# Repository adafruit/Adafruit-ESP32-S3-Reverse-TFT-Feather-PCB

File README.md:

## Adafruit ESP32-S3 Reverse TFT Feather - 4MB Flash, 2MB PSRAM, STEMMA QT PCB

<a href="http://www.adafruit.com/products/5691"><br/>
Click here to purchase one from the Adafruit shop</a>

PCB files for the Adafruit ESP32-S3 Reverse TFT Feather - 4MB Flash, 2MB PSRAM, STEMMA QT. 

Format is EagleCAD schematic and board layout
* https://www.adafruit.com/product/5691

### Description

Like Missy Elliot, we like to "put our [Feather] down, flip it and reverse it" and that's exactly what we've done with this new development board. It's basically our ESP32-S3 TFT Feather but with the 240x135 color TFT display on the back-side not the front-side. That makes it great for panel-mounted projects, particularly since we've also got some space for 3 buttons to go along. It's like an all-in-one display interface dev board, powered by the fantastic ESP32-S3 WIFI module.

This Feather comes with native USB and 4 MB Flash + 2 MB of PSRAM, so it is perfect for use with CircuitPython or Arduino with low-cost WiFi. Native USB means it can act like a keyboard or a disk drive. WiFi means it's awesome for IoT projects. And Feather means it works with the large community of Feather Wings for expandability.

The ESP32-S3 is a highly-integrated, low-power, 2.4 GHz Wi-Fi/BLE System-on-Chip (SoC) solution that has built-in native USB as well as some other interesting new technologies like Time of Flight distance measurements and AI acceleration. With its state-of-the-art power and RF performance, this SoC is an ideal choice for a wide variety of application scenarios relating to the Internet of Things (IoT), wearable electronics, and smart homes.

The Feather ESP32-S3 has a dual-core 240 MHz chip, so it is comparable to ESP32's dual-core. However, there is no Bluetooth Classic support, only Bluetooth LE. This chip is a great step up from the earlier ESP32-S2! This ESP32-S3 mini-module we are using on the Feather comes with 4 MB flash and 2 MB PSRAM, as well as lots of 512KB of SRAM so it's perfect for use with CircuitPython support or any time massive buffers are needed: for fast memory access use SRAM, for slower-but-roomier access use PSRAM. It's also great for use in ESP-IDF or with Arduino support.

The color TFT is connected to the SPI pins and uses additional pins for control that are not exposed to the breakout pads. It's the same display as you see here, with 240x135 pixels and is IPS so you get bright color at any angle. The backlight is also connected to a separate pin so you can PWM the backlight up and down as desired.

For low power usages, the Feather has a second low-dropout 3.3V regulator. The regulator is controlled with a GPIO pin on the enable line and can shut off power to the Stemma QT port and TFT. There is also a separate power pin for the NeoPixel that can be used to disable it for even lower quiescent power. With everything off and in deep sleep mode, the TFT feather uses about 100uA of current.

Features:

* ESP32-S3 Dual Core 240MHz Tensilica processor - the next generation of ESP32-Sx, with native USB so it can act like a keyboard/mouse, MIDI device, disk drive, etc!
* Mini module has FCC/CE certification and comes with 4 MByte of Flash and 2 MByte of PSRAM - you can have huge data buffers
* Color 1.14" IPS TFT with 240x135 pixels - bright and colorful display with ST7789 chipset that can be viewed at any angle angle.
* Three User Tactile buttons - D0, D1, and D2. D0/BOOT0 is also used for entering ROM bootloader mode if necessary.
* Power options - USB type C or Lipoly battery
* Built-in battery charging when powered over USB-C
* LiPoly battery monitor - MAX17048 chip actively monitors your battery for voltage and state of charge / percentage reporting over I2C
* Reset and DFU (BOOT0) buttons to get into the ROM bootloader (which is a USB serial port so you don't need a separate cable!)
* Serial debug output pin (optional, for checking the hardware serial debug console)
* STEMMA QT connector for I2C devices, with switchable power, so you can go into low power mode.
* On/Charge/User LEDs + status NeoPixel with pin-controlled power for low power usage
* Low Power friendly! In deep sleep mode, we can get down to 40~50uA of current draw from the Lipoly connection. Quiescent current is from the power regulator, ESP32-S2 chip, and Lipoly monitor. Turn off the NeoPixel and external I2C/TFT power for the lowest quiescent current draw.
* Works with Arduino or CircuitPython

### License

Adafruit invests time and resources providing this open source design, please support Adafruit and open-source hardware by purchasing products from [Adafruit](https://www.adafruit.com)!

Designed by Limor Fried/Ladyada for Adafruit Industries.

Creative Commons Attribution/Share-Alike, all text above must be included in any redistribution. 
See license.txt for additional details.

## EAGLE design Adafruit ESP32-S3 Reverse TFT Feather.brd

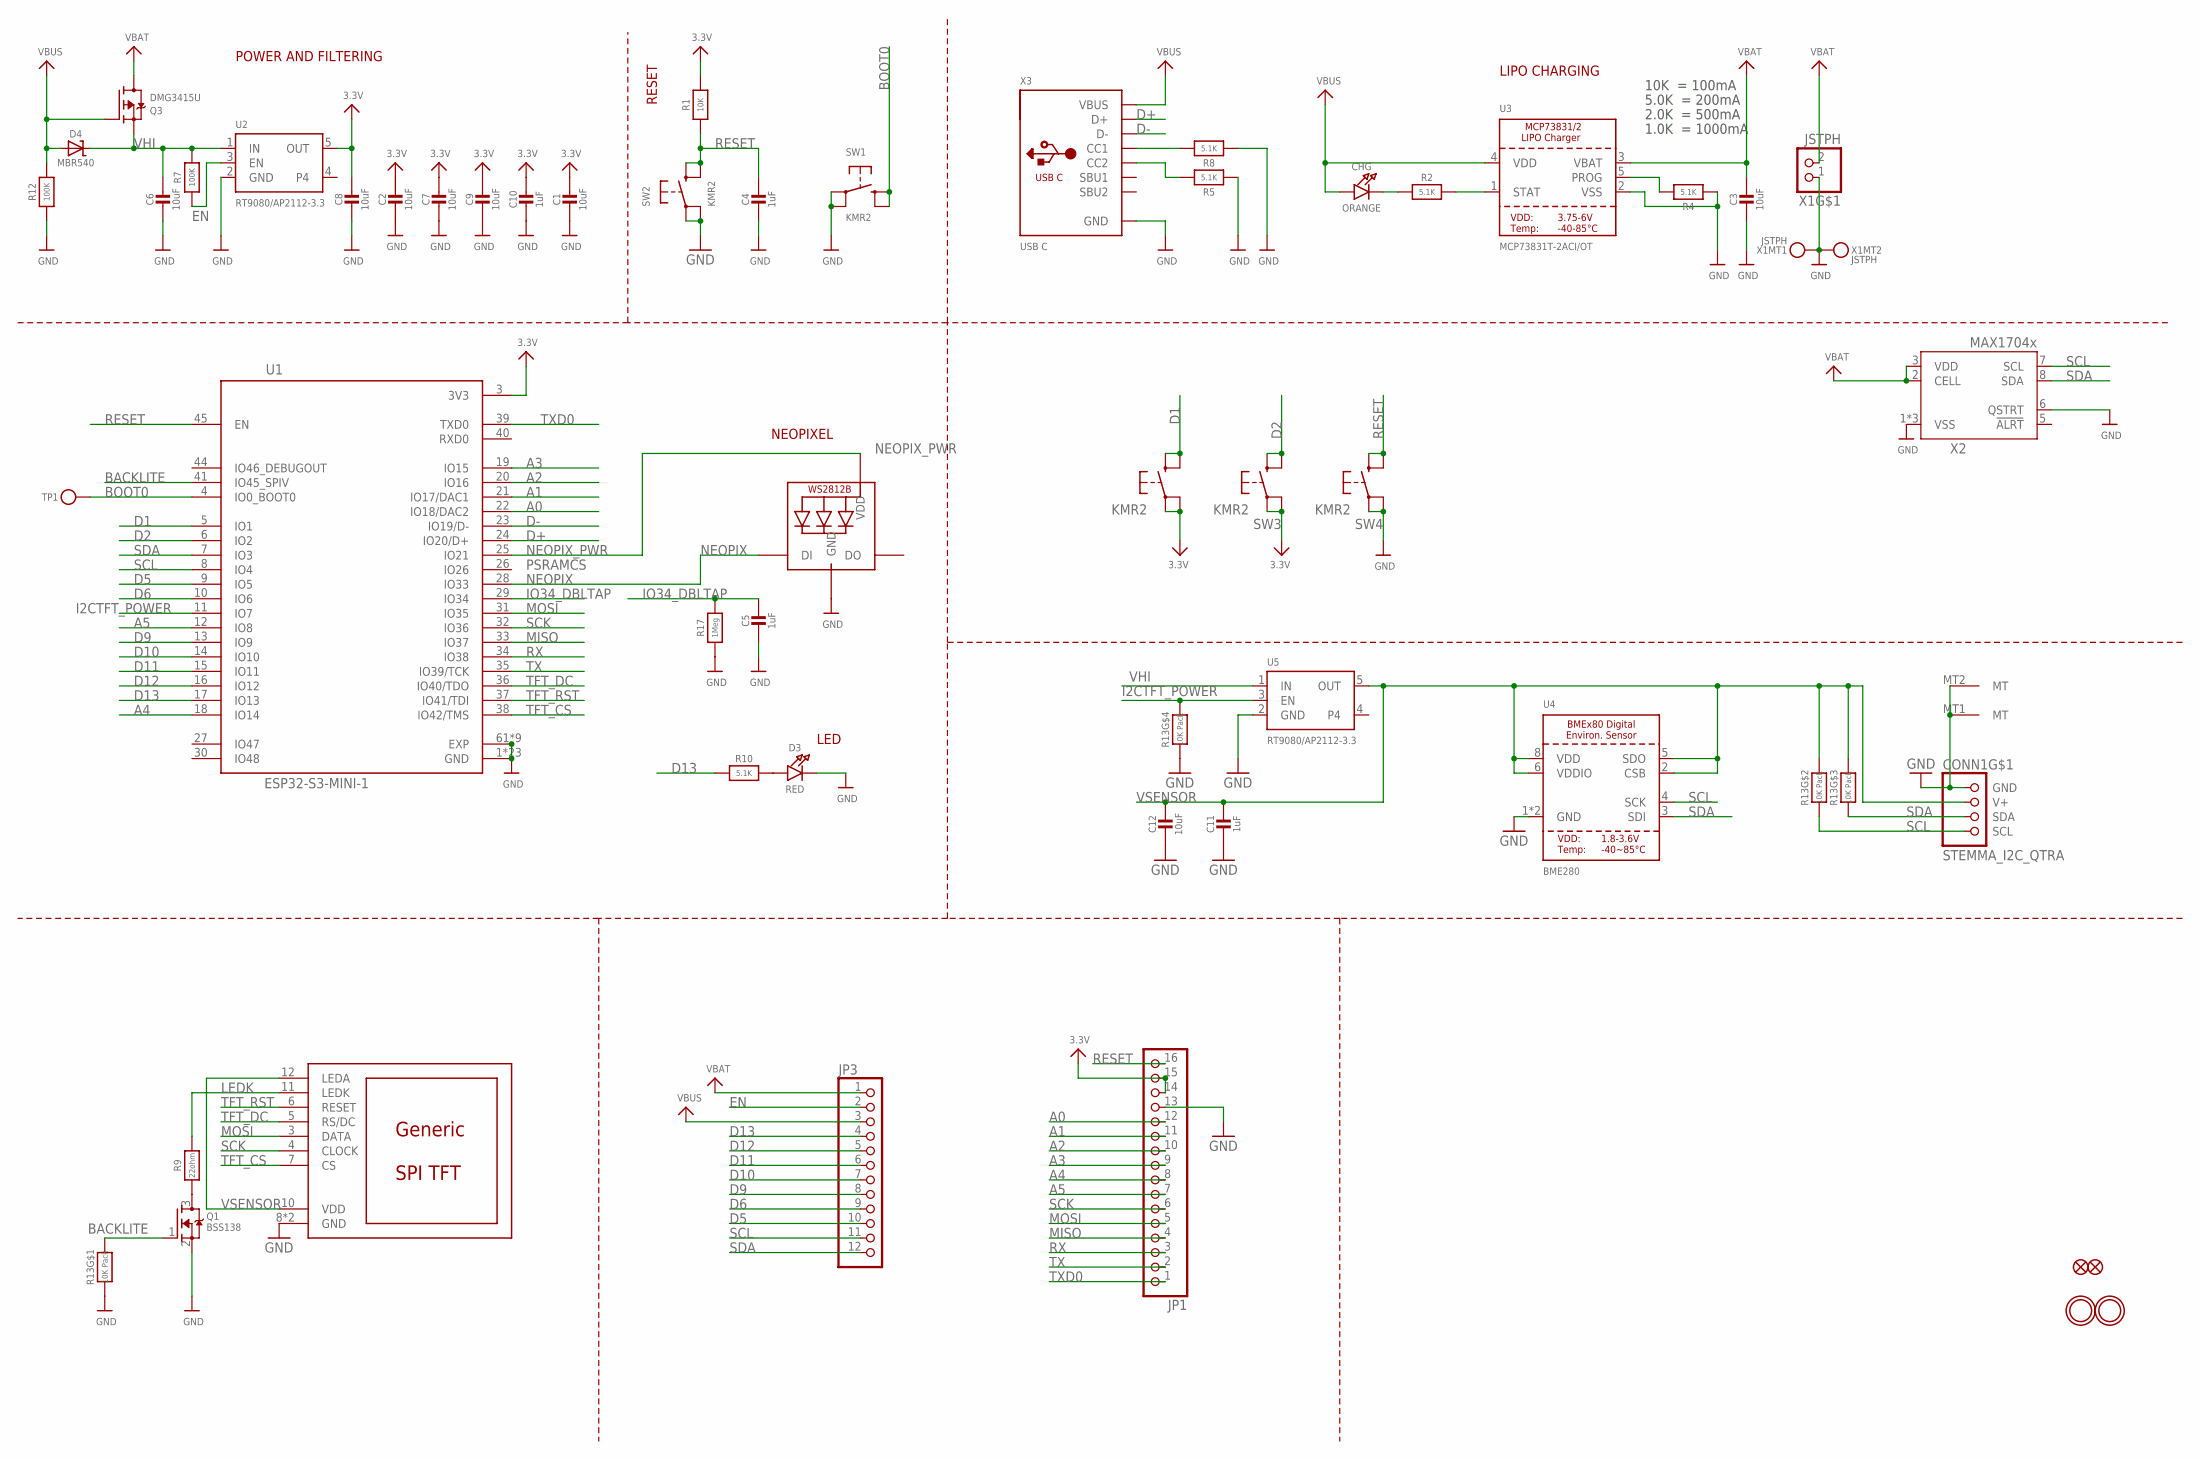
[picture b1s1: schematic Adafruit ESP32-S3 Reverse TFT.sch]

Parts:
C1, C2, C3, C6, C7, C8, C9, C12: 10uF; 0805-NO
C4, C5, C10, C11: 1uF; 0603-NO
CHG: ORANGE; CHIPLED_0603_NOOUTLINE
CONN1: STEMMA_I2C_QTRA; JST_SH4_RA
D3: RED; CHIPLED_0603_NOOUTLINE
D4: MBR540; SOD-123
DISP1: DISP_LCD_GENERIC_SPI_1.14IN_240X135_WRAPUNDER; TFT_1.14IN_240X135_WRAPUNDER
JP1: HEADER-1X16_MIN; 1X16_ROUND_MIN
JP3: HEADER-1X12_MIN; 1X12_ROUND_MIN
LED1: WS2812B_SK6805_1515; SK6805_1515
Q1: BSS138; SC70
Q3: DMG3415U; SOT23-R
R1: 10K; 0603-NO
R2, R4, R5, R8, R10: 5.1K; 0603-NO
R7, R12: 100K; 0603-NO
R9: 22ohm; 0603-NO
R13: 10K Pack; RESPACK_4X0603
R17: 1Meg; 0603-NO
SW1, SW2, SW3, SW4, SW5: KMR2; BTN_RKB2_4.6X2.8
TP1: TESTPOINTROUND1.5MMNO; TESTPOINT_ROUND_1.5MM_NO
U1: ESP32-S3-MINI-1; ESP32-S2-MINI-1
U2, U5: RT9080/AP2112-3.3; SOT23-5; JLC_ROTATION 0
U3: MCP73831T-2ACI/OT; SOT23-5
U4: BME280
U$31, U$32: MOUNTINGHOLE2.5; MOUNTINGHOLE_2.5_PLATED
U$34, U$35: FIDUCIAL_1MM
X1: JSTPH; JSTPH2_BATT
X2: MAX17048/T; TDFN8_2X2MM
X3: USB C; USB_C_CUSB31-CFM2AX-01-X

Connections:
3.3V: C1.1, C2.1, C7.1, C8.1, C9.1, C10.1, JP1.14, JP1.15, R1.2, SW3.A, SW3.A' (P1), SW5.A, SW5.A' (P1), U1.3 (3V3), U2.5 (OUT)
A0: JP1.12, U1.22 (IO18/DAC2)
A1: JP1.11, U1.21 (IO17/DAC1)
A2: JP1.10, U1.20 (IO16)
A3: JP1.9, U1.19 (IO15)
A4: JP1.8, U1.18 (IO14)
A5: JP1.7, U1.12 (IO8)
BACKLITE: Q1.1 (G), R13.8 (2), U1.41 (IO45_SPIV)
BOOT0: SW1.B (S), SW1.B' (S1), TP1.P$1, U1.4 (IO0_BOOT0)
D1: SW5.B (S), SW5.B' (S1), U1.5 (IO1)
D2: SW3.B (S), SW3.B' (S1), U1.6 (IO2)
D5: JP3.10, U1.9 (IO5)
D6: JP3.9, U1.10 (IO6)
D9: JP3.8, U1.13 (IO9)
D10: JP3.7, U1.14 (IO10)
D11: JP3.6, U1.15 (IO11)
D12: JP3.5, U1.16 (IO12)
D13: JP3.4, R10.1, U1.17 (IO13)
D+: U1.24 (IO20/D+), X3.A6 (D+), X3.B6 (D+)
D-: U1.23 (IO19/D-), X3.A7 (D-), X3.B7 (D-)
EN: JP3.2, R7.1, U2.3 (EN)
GND: C1.2, C2.2, C3.2, C4.2, C5.2, C6.2, C7.2, C8.2, C9.2, C10.2, C11.2, C12.2, CONN1.1 (GND), CONN1.MT1 (MT), CONN1.MT2 (MT), D3.C, DISP1.8 (GND), DISP1.13 (GND), JP1.13, LED1.4 (GND), Q1.2 (S), R4.1, R5.1, R8.1, R12.1, R13.1, R13.4 (1), R17.1, SW1.A, SW1.A' (P1), SW2.A, SW2.A' (P1), SW4.A, SW4.A' (P1), U1.1 (GND), U1.2 (GND), U1.42 (GND), U1.43 (GND), U1.46 (GND), U1.47 (GND), U1.48 (GND), U1.49 (GND), U1.50 (GND), U1.51 (GND), U1.52 (GND), U1.53 (GND), U1.54 (GND), U1.55 (GND), U1.56 (GND), U1.57 (GND), U1.58 (GND), U1.59 (GND), U1.60 (GND), U1.61 (EXP), U1.62 (GND), U1.63 (GND), U1.64 (GND), U1.65 (GND), U1.66 (EXP), U1.67 (EXP), U1.68 (EXP), U1.69 (EXP), U1.70 (EXP), U1.71 (EXP), U1.72 (EXP), U1.73 (EXP), U2.2 (GND), U3.2 (VSS), U4.1 (GND), U4.7 (GND), U5.2 (GND), X1.1, X1.NC1, X1.NC2, X2.1 (VSS), X2.4 (VSS), X2.6 (QSTRT), X2.THERMAL (VSS), X3.A1B12 (GND), X3.B1A12 (GND)
I2CTFT_POWER: R13.5 (2), U1.11 (IO7), U5.3 (EN)
IO34_DBLTAP: C5.1, R17.2, U1.29 (IO34)
LEDK: DISP1.11 (LEDK), R9.2
MISO: JP1.4, U1.33 (IO37)
MOSI: DISP1.3 (DATA), JP1.5, U1.31 (IO35)
unnamed: CHG.C, R2.1
unnamed: Q1.3 (D), R9.1
unnamed: R2.2, U3.1 (STAT)
unnamed: R4.2, U3.5 (PROG)
unnamed: D3.A, R10.2
unnamed: R8.2, X3.A5 (CC1)
unnamed: R5.2, X3.B5 (CC2)
NEOPIX: LED1.1 (DI), U1.28 (IO33)
NEOPIX_PWR: LED1.2 (VDD), U1.25 (IO21)
RESET: C4.1, JP1.16, R1.1, SW2.B (S), SW2.B' (S1), SW4.B (S), SW4.B' (S1), U1.45 (EN)
RX: JP1.3, U1.34 (IO38)
SCK: DISP1.4 (CLOCK), JP1.6, U1.32 (IO36)
SCL: CONN1.4 (SCL), JP3.11, R13.2 (1), U1.8 (IO4), U4.4 (SCK), X2.7 (SCL)
SDA: CONN1.3 (SDA), JP3.12, R13.3 (1), U1.7 (IO3), U4.3 (SDI), X2.8 (SDA)
TFT_CS: DISP1.7 (CS), U1.38 (IO42/TMS)
TFT_DC: DISP1.5 (RS/DC), U1.36 (IO40/TDO)
TFT_RST: DISP1.6 (RESET), U1.37 (IO41/TDI)
TX: JP1.2, U1.35 (IO39/TCK)
TXD0: JP1.1, U1.39 (TXD0)
VBAT: C3.1, JP3.1, Q3.3 (D), U3.3 (VBAT), X1.2, X2.2 (CELL), X2.3 (VDD)
VBUS: CHG.A, D4.A, JP3.3, Q3.1 (G), R12.2, U3.4 (VDD), X3.A4B9 (VBUS), X3.B4A9 (VBUS)
VHI: C6.1, D4.C, Q3.2 (S), R7.2, U2.1 (IN), U5.1 (IN)
VSENSOR: C11.1, C12.1, CONN1.2 (V+), DISP1.10 (VDD), DISP1.12 (LEDA), R13.6 (2), R13.7 (2), U4.2 (CSB), U4.5 (SDO), U4.6 (VDDIO), U4.8 (VDD), U5.5 (OUT)

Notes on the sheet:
POWER AND FILTERING
RESET
10K = 100mA
5.0K = 200mA
2.0K = 500mA
1.0K = 1000mA
LIPO CHARGING
LED
PSRAMCS
NEOPIXEL

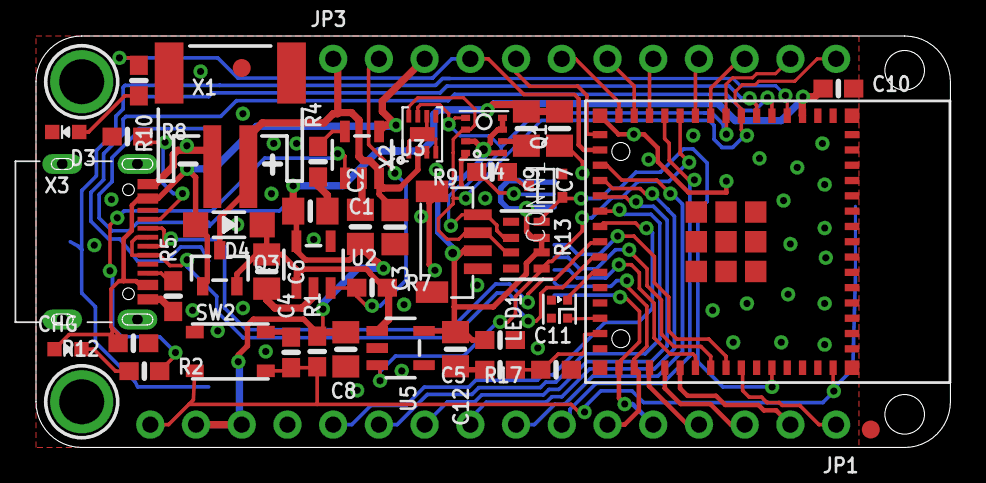
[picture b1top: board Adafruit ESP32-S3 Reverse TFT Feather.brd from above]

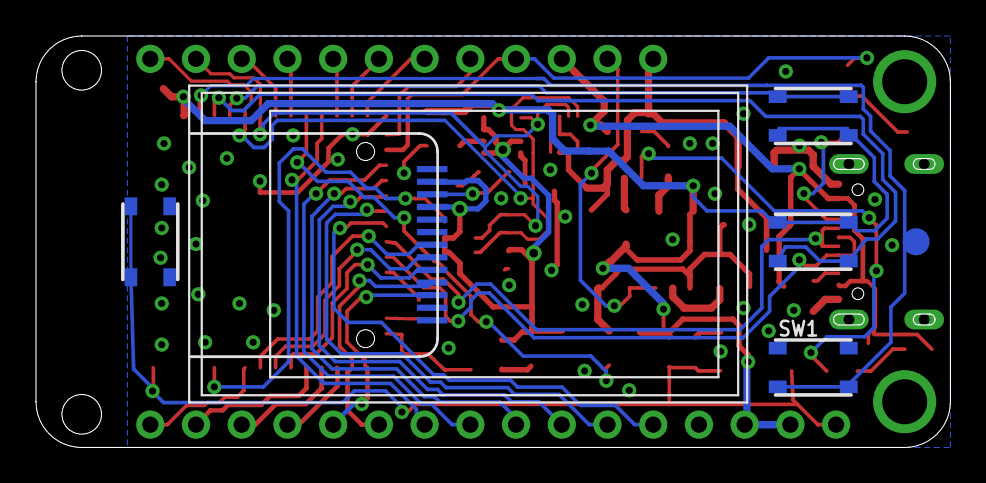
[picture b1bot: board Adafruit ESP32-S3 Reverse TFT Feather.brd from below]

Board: 2 copper layers, 50.8 x 22.9 mm, 88 parts (11 on the bottom side), 50 nets.

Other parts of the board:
PLABEL0: PLABEL0
PLABEL1: PLABEL1
PLABEL2: PLABEL2
PLABEL3: PLABEL3
PLABEL4: PLABEL4
PLABEL5: PLABEL5
PLABEL6: PLABEL6
PLABEL7: PLABEL7
PLABEL8: PLABEL8
PLABEL9: PLABEL9
PLABEL10: PLABEL10
PLABEL11: PLABEL11
PLABEL12: PLABEL12
PLABEL13: PLABEL13
PLABEL14: PLABEL14
PLABEL15: PLABEL15
PLABEL16: PLABEL16
PLABEL17: PLABEL17
PLABEL18: PLABEL18
PLABEL19: PLABEL19
PLABEL20: PLABEL20
PLABEL21: PLABEL21
PLABEL22: PLABEL22
PLABEL23: PLABEL23
PLABEL24: PLABEL24
PLABEL25: PLABEL25
PLABEL26: PLABEL26
PLABEL27: PLABEL27
PLABEL28: PLABEL28
PLABEL29: PLABEL29
PLABEL30: PLABEL30
PLABEL31: PLABEL31
PLABEL33: PLABEL33
PLABEL34: PLABEL34
PLABEL35: PLABEL35
PLABEL36: PLABEL36
PLABEL37: PLABEL37

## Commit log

2023-03-01 adding cookiecutter output
2023-03-01 updating eagle file names
2023-03-01 adding prettypins pdfs
2023-10-31 updating factory reset
    more responsive buttons
2024-10-25 svgs
2024-10-25 correct red and black dots next to battery charge connector
2025-09-23 Correct battery connector

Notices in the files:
parts and their libraries:
microbuilder: This work is placed in the public domain, and may be freely used for commercial and non-commercial work with the following conditions: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
COPYRIGHT: Copyright (C) 2018 Accelerated Designs. All rights reserved
